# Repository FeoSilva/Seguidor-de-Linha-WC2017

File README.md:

# Marcos John - Seguidor-de-Linha-WC2017

O robô do Seguidor de Linha que participou do Winter Challenge edição 13 em 2017 está dividido em:
- Mecânica (Arquivos em CADs do robô projetado no SolidWorks 2016)
- Eletrônica (PCB projetada no Autodesk Eagle e confeccionada com a CNC OtherMill)
- Software (Programação do robô feita na IDE do Arduino)

Componentes do robô:
- Arduino Nano (Microcontrolador)
- <a href="https://www.pololu.com/product/960">QTR Array Analógico - Pololu (Sensor para Seguir Linha)</a>
- <a href="https://www.pololu.com/product/713">TB6612FNG - Pololu (Driver do Motor) </a>
- <a href="https://www.pololu.com/product/1098">50:1 Micro Metal Gearmotor LP 6V (Motores)</a>
- Bateria Li-Po 2S 7.4 - Turnigy

Agradecimentos: <br>
<a href="https://github.com/marcosdeoliveira">Marcos Oliveira</a><br>
<a href="https://github.com/joaopedrovbs">João Pedron Vilas Boas</a>

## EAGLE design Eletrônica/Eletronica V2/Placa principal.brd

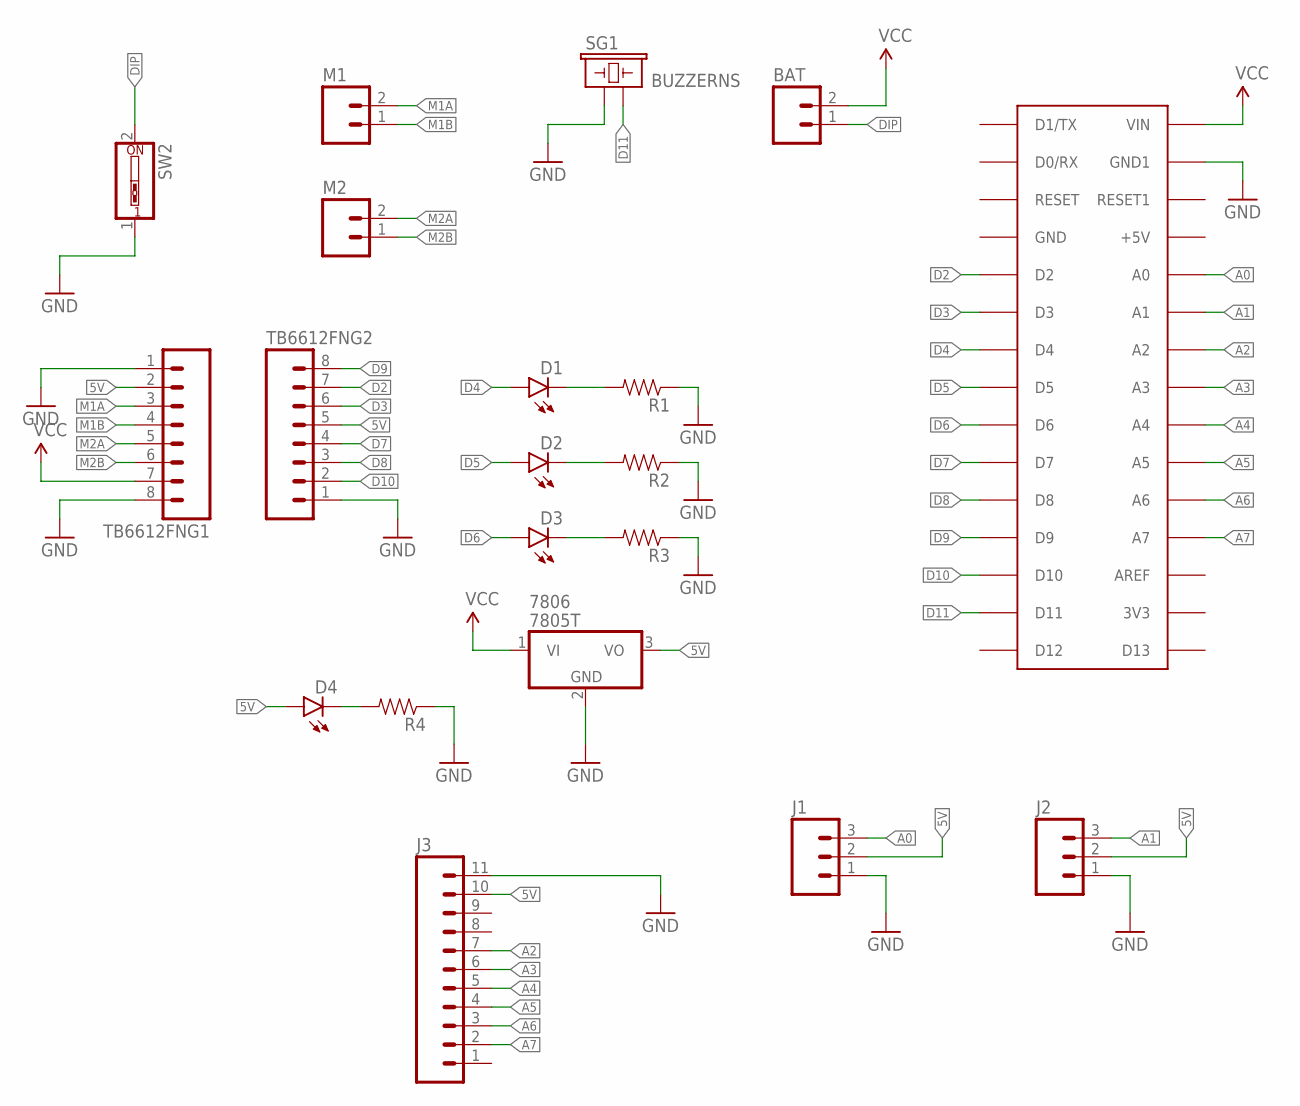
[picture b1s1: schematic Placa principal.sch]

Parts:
7806: 7805T; TO220H
BAT: M02PTH; 1X02
D1, D2, D3, D4: LED5MM
J1, J2: M03PTH; 1X03
J3: M11PTH; 1X11
M1, M2: M02JST-PTH-VERT; JST-2-PTH-VERT
R1, R2, R3, R4: RESISTOREZ; AXIAL-0.3EZ
SG1: BUZZERNS; BUZZER-12MM-NS
SW2: SW_DIP-1; EDG-01
TB6612FNG1, TB6612FNG2: M08; 1X08_ROUND
U$2: ARDUINONANO; PDIP-32

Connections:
5V: 7806.3 (VO), D4.A, J1.2, J2.2, J3.10, TB6612FNG1.2, TB6612FNG2.5
A0: J1.3, U$2.A0
A1: J2.3, U$2.A1
A2: J3.7, U$2.A2
A3: J3.6, U$2.A3
A4: J3.5, U$2.A4
A5: J3.4, U$2.A5
A6: J3.3, U$2.A6
A7: J3.2, U$2.A7
D2: TB6612FNG2.7, U$2.D2
D3: TB6612FNG2.6, U$2.D3
D4: D1.A, U$2.D4
D5: D2.A, U$2.D5
D6: D3.A, U$2.D6
D7: TB6612FNG2.4, U$2.D7
D8: TB6612FNG2.3, U$2.D8
D9: TB6612FNG2.8, U$2.D9
D10: TB6612FNG2.2, U$2.D10
D11: SG1.- (2), U$2.D11
DIP: BAT.1, SW2.2
GND: 7806.2 (GND), J1.1, J2.1, J3.11, R1.P$1 (1), R2.P$1 (1), R3.P$1 (1), R4.P$1 (1), SG1.+ (1), SW2.1, TB6612FNG1.1, TB6612FNG1.8, TB6612FNG2.1, U$2.GND1
M1A: M1.2, TB6612FNG1.3
M1B: M1.1, TB6612FNG1.4
M2A: M2.2, TB6612FNG1.5
M2B: M2.1, TB6612FNG1.6
unnamed: D4.K (C), R4.P$2 (2)
unnamed: D1.K (C), R1.P$2 (2)
unnamed: D2.K (C), R2.P$2 (2)
unnamed: D3.K (C), R3.P$2 (2)
VCC: 7806.1 (VI), BAT.2, TB6612FNG1.7, U$2.VIN

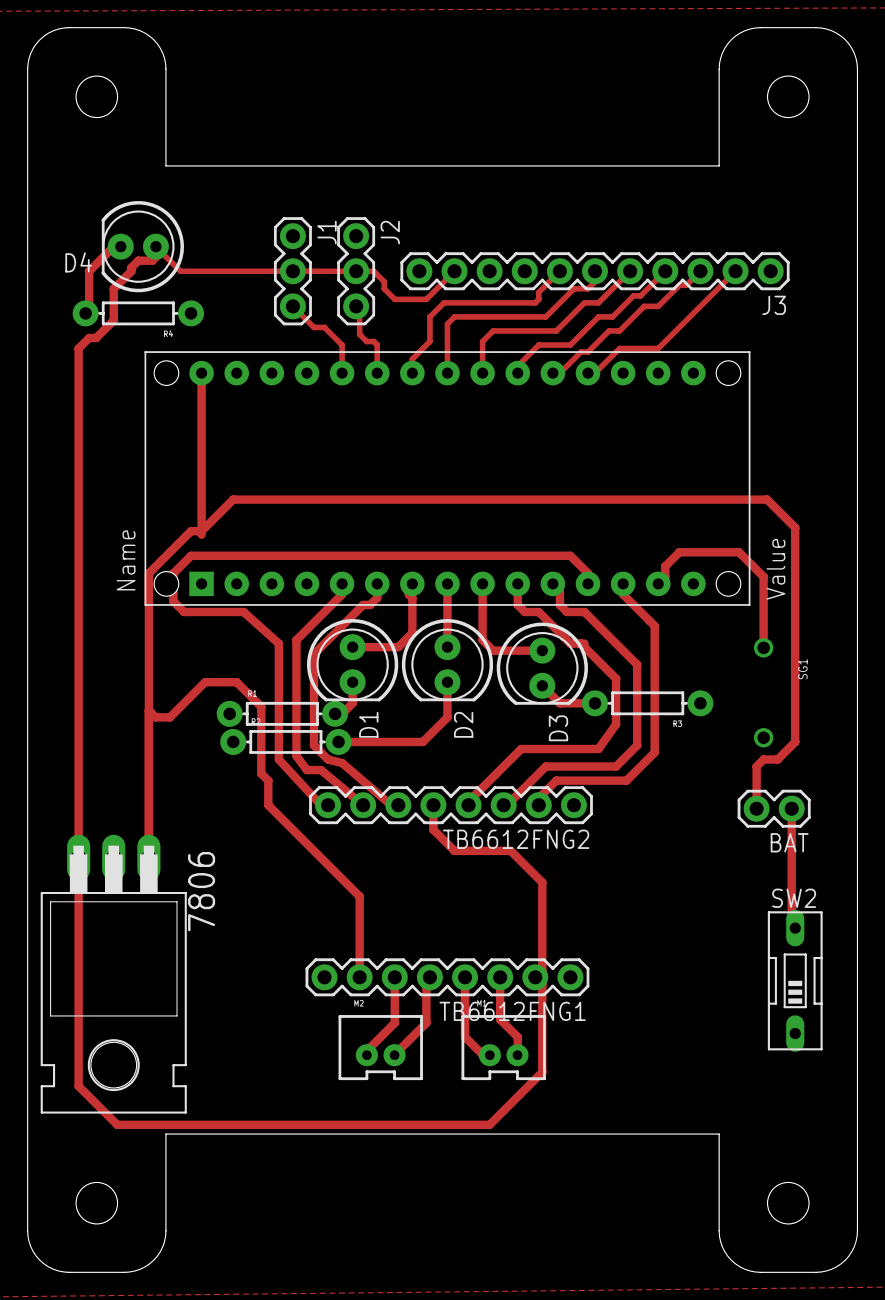
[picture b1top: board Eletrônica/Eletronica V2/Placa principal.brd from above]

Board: 2 copper layers, 60.0 x 90.0 mm, 20 parts (0 on the bottom side), 30 nets.

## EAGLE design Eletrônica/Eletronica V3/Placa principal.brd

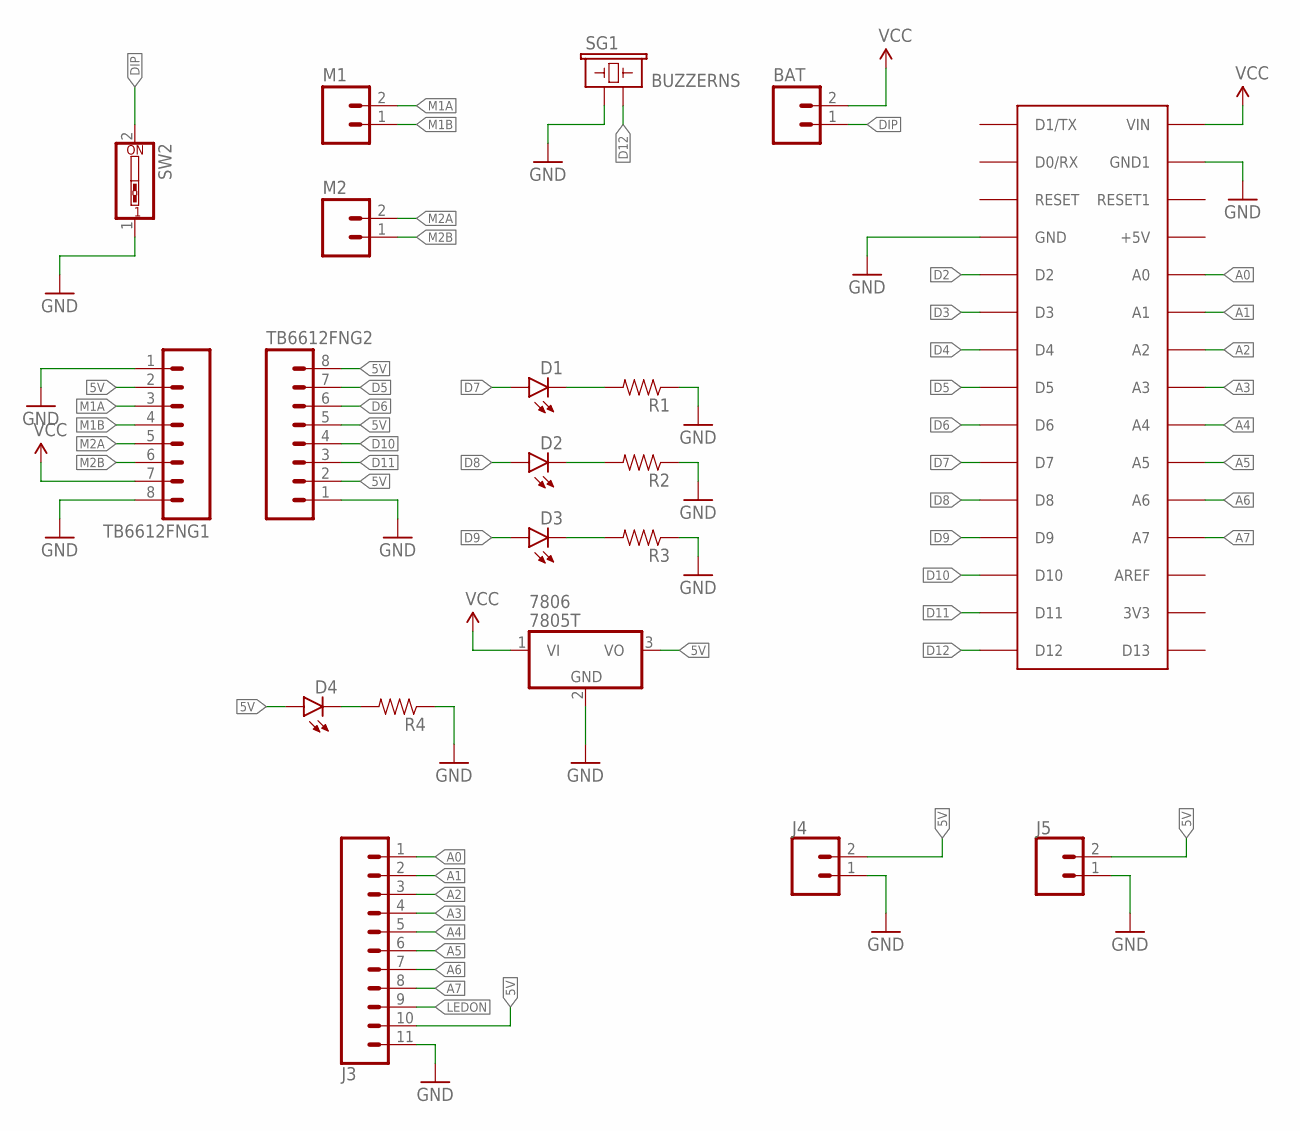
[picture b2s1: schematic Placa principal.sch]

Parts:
7806: 7805T; TO220H
BAT: M02PTH; 1X02@1
D1, D2, D3, D4: LED5MM
J3: CONN_11; 1X11
J4, J5: CONN_02; 1X02
M1, M2: M02JST-PTH-VERT; JST-2-PTH-VERT
R1, R2, R3, R4: RESISTOREZ; AXIAL-0.3EZ
SG1: BUZZERNS; BUZZER-12MM-NS
SW2: SW_DIP-1; EDG-01
TB6612FNG1, TB6612FNG2: M08; 1X08_ROUND
U1: NANO; PDIP-32

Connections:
5V: 7806.3 (VO), D4.A, J3.10, J4.2, J5.2, TB6612FNG1.2, TB6612FNG2.2, TB6612FNG2.5, TB6612FNG2.8
A0: J3.1, U1.A0
A1: J3.2, U1.A1
A2: J3.3, U1.A2
A3: J3.4, U1.A3
A4: J3.5, U1.A4
A5: J3.6, U1.A5
A6: J3.7, U1.A6
A7: J3.8, U1.A7
D2: U1.D2
D3: U1.D3
D4: U1.D4
D5: TB6612FNG2.7, U1.D5
D6: TB6612FNG2.6, U1.D6
D7: D1.A, U1.D7
D8: D2.A, U1.D8
D9: D3.A, U1.D9
D10: TB6612FNG2.4, U1.D10
D11: TB6612FNG2.3, U1.D11
D12: SG1.- (2), U1.D12
DIP: BAT.1, SW2.2
GND: 7806.2 (GND), J3.11, J4.1, J5.1, R1.P$1 (1), R2.P$1 (1), R3.P$1 (1), R4.P$1 (1), SG1.+ (1), SW2.1, TB6612FNG1.1, TB6612FNG1.8, TB6612FNG2.1, U1.GND, U1.GND1
LEDON: J3.9
M1A: M1.2, TB6612FNG1.3
M1B: M1.1, TB6612FNG1.4
M2A: M2.2, TB6612FNG1.5
M2B: M2.1, TB6612FNG1.6
unnamed: D4.K (C), R4.P$2 (2)
unnamed: D1.K (C), R1.P$2 (2)
unnamed: D2.K (C), R2.P$2 (2)
unnamed: D3.K (C), R3.P$2 (2)
VCC: 7806.1 (VI), BAT.2, TB6612FNG1.7, U1.VIN

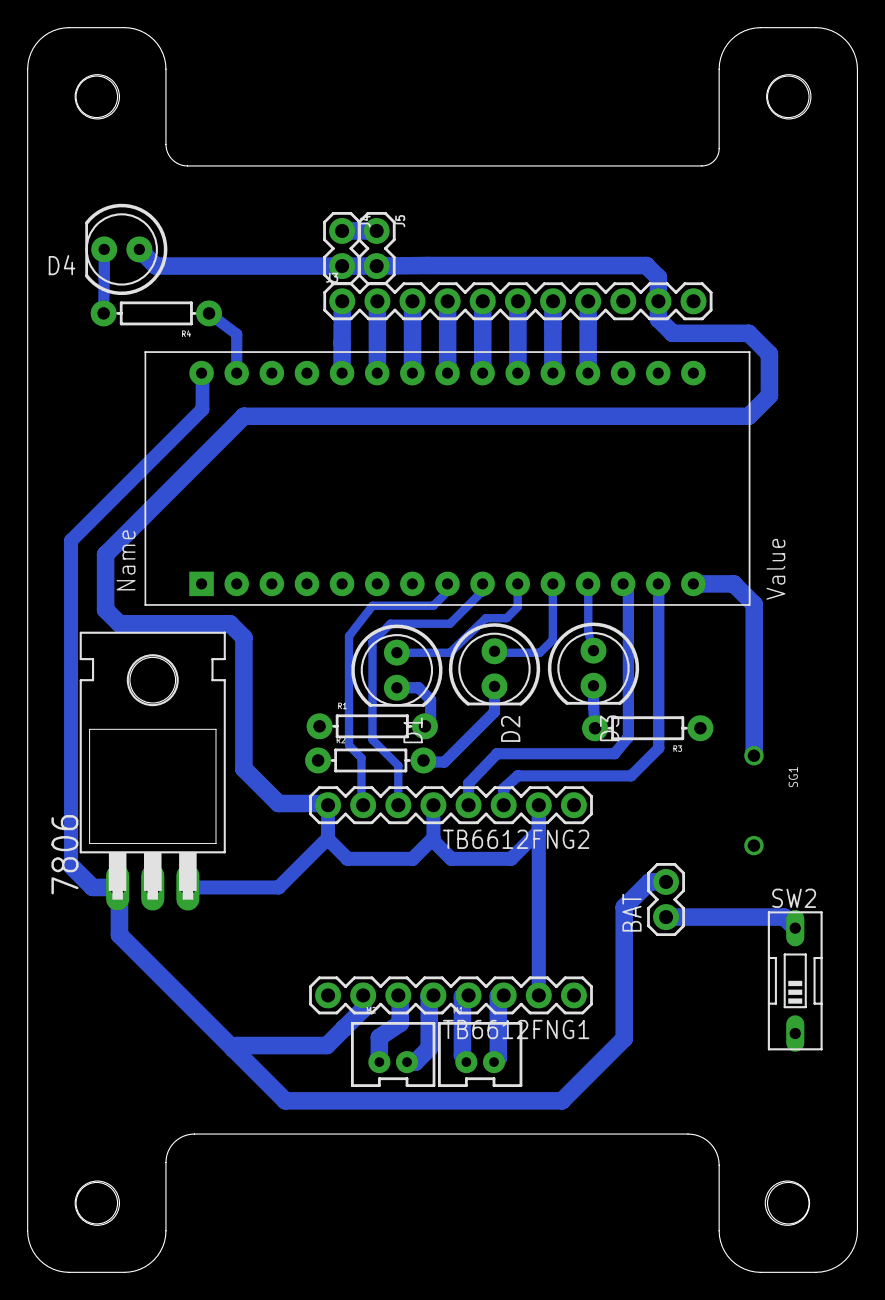
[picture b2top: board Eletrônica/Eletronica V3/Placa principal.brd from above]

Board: 2 copper layers, 60.0 x 90.0 mm, 20 parts (0 on the bottom side), 28 nets.

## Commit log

2017-07-03 Initial Commit and Configs
2017-07-03 PID Line Follower
2017-07-07 Change contants of PID
2017-07-07 Round 1 - 07.07.2017
2017-07-09 Final Code - Winter Challenge 2017
2017-07-09 All files of the final version - Marcos John
2017-07-09 Midia Files

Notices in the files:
parts and their libraries:
SparkFun-Connectors: Licensing: Creative Commons ShareAlike 4.0 International - https://creativecommons.org/licenses/by-sa/4.0
